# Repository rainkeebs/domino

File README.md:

# domino
 3x10 keyboard

all these files are presented as is with no extra effort on my part to pretty them up or verify anything. please dont ask me any questions about this, i dont care enough to answer. license is unlicense, use as you like. i am not liable for *any* use of this dont even try. x

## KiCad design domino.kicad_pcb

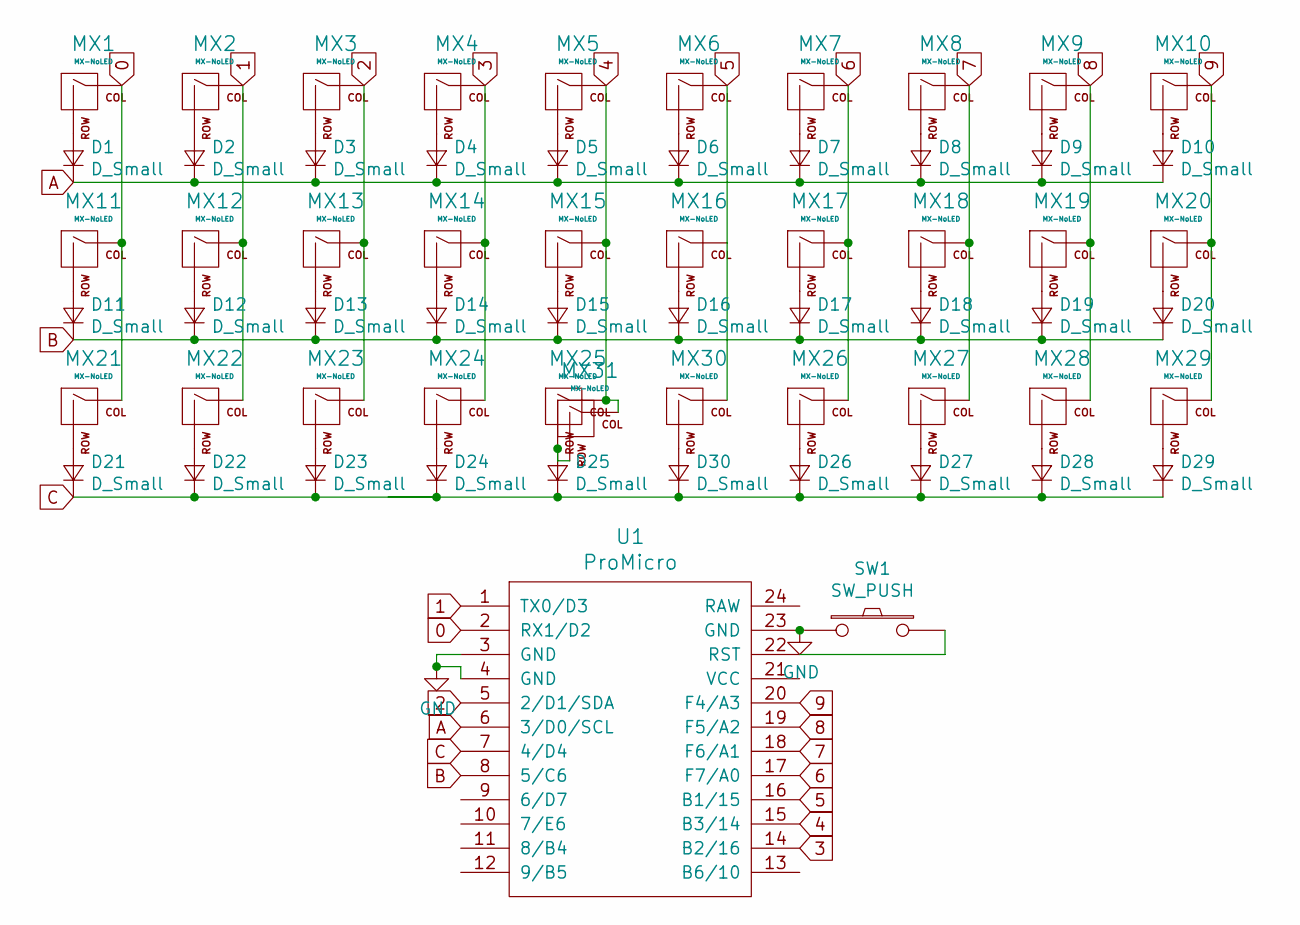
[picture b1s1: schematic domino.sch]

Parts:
D1, D2, D3, D4, D5, D6, D7, D8, D9, D10, D11, D12, D13, D14, D15, D16, D17, D18, D19, D20, D21, D22, D23, D24, D25, D26, D27, D28, D29, D30: D_Small; Diode-Hybrid-Back
MX1, MX2, MX3, MX4, MX5, MX6, MX7, MX8, MX9, MX10, MX11, MX12, MX13, MX14, MX15, MX16, MX17, MX18, MX19, MX20, MX21, MX22, MX23, MX24, MX26, MX27, MX28, MX29, MX30, MX31: MX-NoLED; MXOnly-1U-NoLED
MX25: MX-NoLED; MXOnly-2U-ReversedStabilizers-NoLED
SW1: SW_PUSH; tht-reset
U1: ProMicro; promicro-good

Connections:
0: MX1.1 (COL), MX11.1 (COL), MX21.1 (COL), U1.2 (RX1/D2)
1: MX2.1 (COL), MX12.1 (COL), MX22.1 (COL), U1.1 (TX0/D3)
2: MX3.1 (COL), MX13.1 (COL), MX23.1 (COL), U1.5 (2/D1/SDA)
3: MX4.1 (COL), MX14.1 (COL), MX24.1 (COL), U1.14 (B2/16)
4: MX5.1 (COL), MX15.1 (COL), MX25.1 (COL), MX31.1 (COL), U1.15 (B3/14)
5: MX6.1 (COL), MX16.1 (COL), MX30.1 (COL), U1.16 (B1/15)
6: MX7.1 (COL), MX17.1 (COL), MX26.1 (COL), U1.17 (F7/A0)
7: MX8.1 (COL), MX18.1 (COL), MX27.1 (COL), U1.18 (F6/A1)
8: MX9.1 (COL), MX19.1 (COL), MX28.1 (COL), U1.19 (F5/A2)
9: MX10.1 (COL), MX20.1 (COL), MX29.1 (COL), U1.20 (F4/A3)
A: D1.1 (K), D2.1 (K), D3.1 (K), D4.1 (K), D5.1 (K), D6.1 (K), D7.1 (K), D8.1 (K), D9.1 (K), D10.1 (K), U1.6 (3/D0/SCL)
B: D11.1 (K), D12.1 (K), D13.1 (K), D14.1 (K), D15.1 (K), D16.1 (K), D17.1 (K), D18.1 (K), D19.1 (K), D20.1 (K), U1.8 (5/C6)
C: D21.1 (K), D22.1 (K), D23.1 (K), D24.1 (K), D25.1 (K), D26.1 (K), D27.1 (K), D28.1 (K), D29.1 (K), D30.1 (K), U1.7 (4/D4)
GND: SW1.1, U1.3 (GND), U1.4 (GND), U1.23 (GND)
unnamed: D1.2 (A), MX1.2 (ROW)
unnamed: D2.2 (A), MX2.2 (ROW)
unnamed: D3.2 (A), MX3.2 (ROW)
unnamed: D4.2 (A), MX4.2 (ROW)
unnamed: D5.2 (A), MX5.2 (ROW)
unnamed: D6.2 (A), MX6.2 (ROW)
unnamed: D7.2 (A), MX7.2 (ROW)
unnamed: D8.2 (A), MX8.2 (ROW)
unnamed: D9.2 (A), MX9.2 (ROW)
unnamed: D10.2 (A), MX10.2 (ROW)
unnamed: D11.2 (A), MX11.2 (ROW)
unnamed: D12.2 (A), MX12.2 (ROW)
unnamed: D13.2 (A), MX13.2 (ROW)
unnamed: D14.2 (A), MX14.2 (ROW)
unnamed: D15.2 (A), MX15.2 (ROW)
unnamed: D16.2 (A), MX16.2 (ROW)
unnamed: D17.2 (A), MX17.2 (ROW)
unnamed: D18.2 (A), MX18.2 (ROW)
unnamed: D19.2 (A), MX19.2 (ROW)
unnamed: D20.2 (A), MX20.2 (ROW)
unnamed: D21.2 (A), MX21.2 (ROW)
unnamed: D22.2 (A), MX22.2 (ROW)
unnamed: D23.2 (A), MX23.2 (ROW)
unnamed: D24.2 (A), MX24.2 (ROW)
unnamed: D25.2 (A), MX25.2 (ROW), MX31.2 (ROW)
unnamed: D26.2 (A), MX26.2 (ROW)
unnamed: D27.2 (A), MX27.2 (ROW)
unnamed: D28.2 (A), MX28.2 (ROW)
unnamed: D29.2 (A), MX29.2 (ROW)
unnamed: D30.2 (A), MX30.2 (ROW)
unnamed: SW1.2, U1.22 (RST)

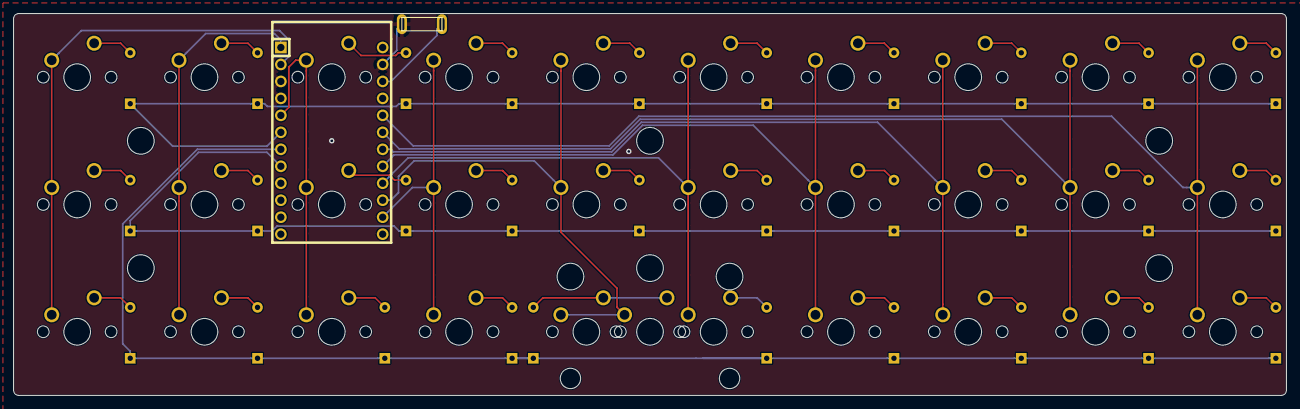
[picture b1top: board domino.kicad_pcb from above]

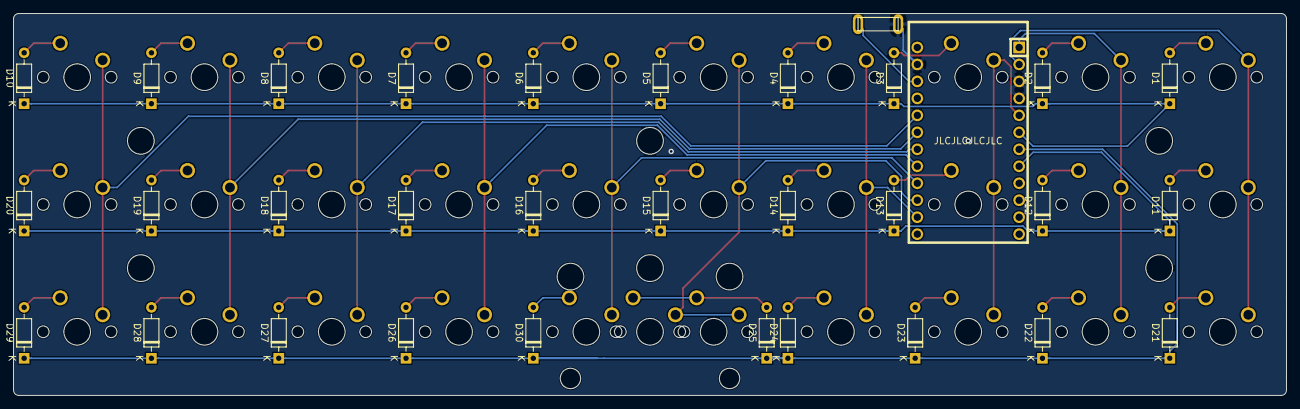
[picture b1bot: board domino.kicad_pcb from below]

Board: 2 copper layers, 190.5 x 57.2 mm, 63 parts (30 on the bottom side), 45 nets.

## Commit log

2020-11-06 this is it
2020-11-07 uhhh
2020-11-15 Update fp-info-cache
